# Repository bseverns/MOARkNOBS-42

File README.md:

# MOARkNOBS-42

MOARkNOBS-42 (MN42) is an open, reactive MIDI/OSC performance instrument: a physical control surface, Teensy firmware,
a browser configurator, and a desktop Bridge that are designed and documented as one system.

It gives performers 42 configurable control slots, six envelope-follower inputs, profile recall, MIDI, OSC, and
browser-based editing without hiding the device contract behind proprietary software. It is closer to a small system
with a very visible control surface than “just a controller with a lot of knobs.”

[Try the browser configurator in simulator mode](https://bseverns.github.io/MN42/) without hardware, or read the
[five-minute orientation](docs/getting-started/FirstFiveMinutes.md).

## How the system fits together

```mermaid
flowchart LR
  H[Hardware<br>buttons, pots, LEDs,<br>envelope inputs] --> F[Firmware<br>scanning, MIDI,<br>config, persistence]
  F --> C[Contracts<br>manifest, schema,<br>WebSerial, Bridge RPC]
  C --> U[User tools<br>browser configurator,<br>OSC and host MIDI]
```

Each layer reports what it knows to the next. That is why the project emphasizes schema compatibility, verified
readback, test coverage, and evidence-backed support boundaries.

## Choose your path

| Interest | Start here | You will learn... |
| --- | --- | --- |
| Performer | [Quickstart for Performers](docs/getting-started/QuickstartForPerformers.md) | How to connect, configure, recall profiles, and prepare a rig. |
| Builder | [Quickstart for Builders](docs/getting-started/QuickstartForBuilders.md) | How to inspect, flash, bring up, and validate a board. |
| Contributor | [Contributing](CONTRIBUTING.md) | The build, test, documentation, and review gates. |
| Technical Evaluator | [Hardware-Test Readme](HARDWARE_TEST_README.md) | What the current prototype evidence proves—and does not prove. |

For a conceptual tour, use [Start Here](docs/getting-started/StartHere.md). For a complete source-tree map, use
[Repository Contents](docs/project/RepositoryContents.md).

## What is included

- **Hardware:** a Teensy 4.0 control surface with buttons, pots, LEDs, MIDI I/O, OLED feedback, and six reactive inputs.
- **Firmware:** scheduling, control scanning, MIDI behavior, modulation, configuration, and generation-checked persistence.
- **Browser configurator:** direct WebSerial setup, monitoring, staged edits, verified Apply, profiles, and a hardware-free simulator.
- **Bridge:** local browser console, OSC routing, virtual/host MIDI routing, and an App-over-Bridge transport.
- **Documentation and evidence:** contracts, build guides, validation procedures, and dated bench receipts.

## Quick start without hardware

1. Open the [hosted configurator](https://bseverns.github.io/MN42/).
2. Select **Start Simulator** for the firmware-default reset state, or **Load Demo Rig** for the illustrative example.
3. Check the named simulator fixture in Session, then change a slot, inspect the staged diff, and apply it to the simulated device.

The simulator demonstrates the browser workflow. It does not validate physical controls, timing, MIDI wiring, or
electrical behavior.

## Build and test

The PlatformIO project root is `firmware/`; always pass `-d firmware` from the repository root:

```bash
pio run -d firmware -e teensy40_main
pio test -d firmware -e teensy40_unity -vvv
```

Run the grouped repository checks before proposing a change:

```bash
./tools/doctor --full
```

See [Contributing](CONTRIBUTING.md) for the scoped test matrix and the custom Unity transport rules.

## Current project boundary

MN42 is at the hardware-test stage. The prototype boards and software paths are useful for bring-up and evaluation,
but the repository does not claim a public v1.0 release, an orderable fabrication package, universal host/browser
support, or a signed desktop installer.

Current hardware observations, board photos, test status, and the exact evidence still needed are kept in the
[Hardware-Test Readme](HARDWARE_TEST_README.md) and [Current Build](hardware/CurrentBuild.md)—not on this landing page.

## Documentation

- [Documentation site](https://bseverns.github.io/MOARkNOBS-42/)
- [System Map](docs/getting-started/SystemMap.md)
- [Connectivity Guide](docs/getting-started/ConnectivityGuide.md)
- [Documentation Truth Map](docs/reference/DocumentationTruthMap.md)
- [Testing](docs/validation/TESTING.md)
- [Release and reproducibility](REPRODUCIBILITY.md)

If two documents disagree, the [Documentation Truth Map](docs/reference/DocumentationTruthMap.md) defines the tie-break
rules. Historical wiki pages are frozen; canonical maintained documentation lives in this repository and the generated
documentation site.

## Contact and feedback

- Reproducible bugs and public questions: [GitHub Issues](https://github.com/bseverns/MOARkNOBS-42/issues)
- Security-sensitive reports: [Security policy](SECURITY.md)
- Pilot-run inquiries: [severns3@gmail.com](mailto:severns3@gmail.com)

Never put credentials, private device data, or other secrets in a public issue.

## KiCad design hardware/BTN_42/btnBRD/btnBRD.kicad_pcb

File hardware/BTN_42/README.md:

# BTN_42 Hardware

> The button board that turns the firmware's dreams into something you can actually solder. Pure DIY attitude.

## MN42-1

The `MN42-1` folder holds the first PCB revision:

- [BOM_btnBRD_btnBRD_2025-04-17.xlsx](MN42-1/BOM_btnBRD_btnBRD_2025-04-17.xlsx) – complete bill of materials.
- [PickAndPlace_btnBRD_2025-04-17.xlsx](MN42-1/PickAndPlace_btnBRD_2025-04-17.xlsx) – reference positions for automated assembly.
- [Gerber_btnBRD_2025-04-17.zip](MN42-1/Gerber_btnBRD_2025-04-17.zip) – ready-to-send fabrication package.
- `shell/` – STEP and STL models of the enclosure. `3DShell_btnBRD/` holds the STEP files, while `stl/` contains printable STL meshes.

Sketch diagrams live in [`sketch/`](sketch/). The `PNG_btnBRD_2025-07-22` folder contains exported PNG screenshots of the full EasyEDA schematic.

### Sketch Documents

* [buttonMatrix.md](sketch/buttonMatrix.md)
* [power&protection.md](sketch/power&protection.md)
* [teensy&headers.md](sketch/teensy&headers.md)
* [led&midiOut.md](sketch/led&midiOut.md)
* [midiOpto.md](sketch/midiOpto.md)
* [envelopeFE.md](sketch/envelopeFE.md)
* [display.md](sketch/display.md)

Below is a summary of the schematic sheets:

| Sheet # | Title                                  | Contents                                                                                       |
| ------- | -------------------------------------- | ---------------------------------------------------------------------------------------------- |
| 1       | Title / Block Diagram                  | Topology overview; signal & power flow.                                                        |
| 2       | **Power & Protection**                 | DC jack, F1 logic PTC, TVS, bulk caps, F2 LED PTC, VLED cap, regulators note (Teensy onboard). |
| 3       | **Teensy Core & Headers**              | Teensy 4.0 pinout subset used; I2C to OLED; SPI/unused pads; boot/reset.                       |
| 4       | **Key Matrix & MUX**                   | 42 switches + diodes; 2×CD74HC4067 (or # actually used); row/col nets labelled; OE pull-ups.   |
| 5       | **Level-Shifter & LED / MIDI OUT**     | SN74HCT245, RLED 33 Ω, MIDI OUT loop resistors, DIN connector.                                 |
| 6       | **MIDI IN Opto + ESD**                 | 6N138 (or alt), input resistors, 3V3 pull-up, optional activity LED.                           |
| 7       | **Envelope Follower Analog Front-End** | 6 channels: audio jack (or header), rectifier, RC, clamp to 3V3, into ADC pins.                |
| 8       | **Display, UI, Aux Headers**           | SSD1306 (I²C), spare expansion header (5V, 3V3, SDA, SCL, GND), debug SWD pads.                |
| 9       | Netlist summary / BOM cross-ref.       |                                                                                                |

## License

All hardware files are released under the MIT License, matching the rest of this repository. See the [LICENSE](../../LICENSE) file for details.

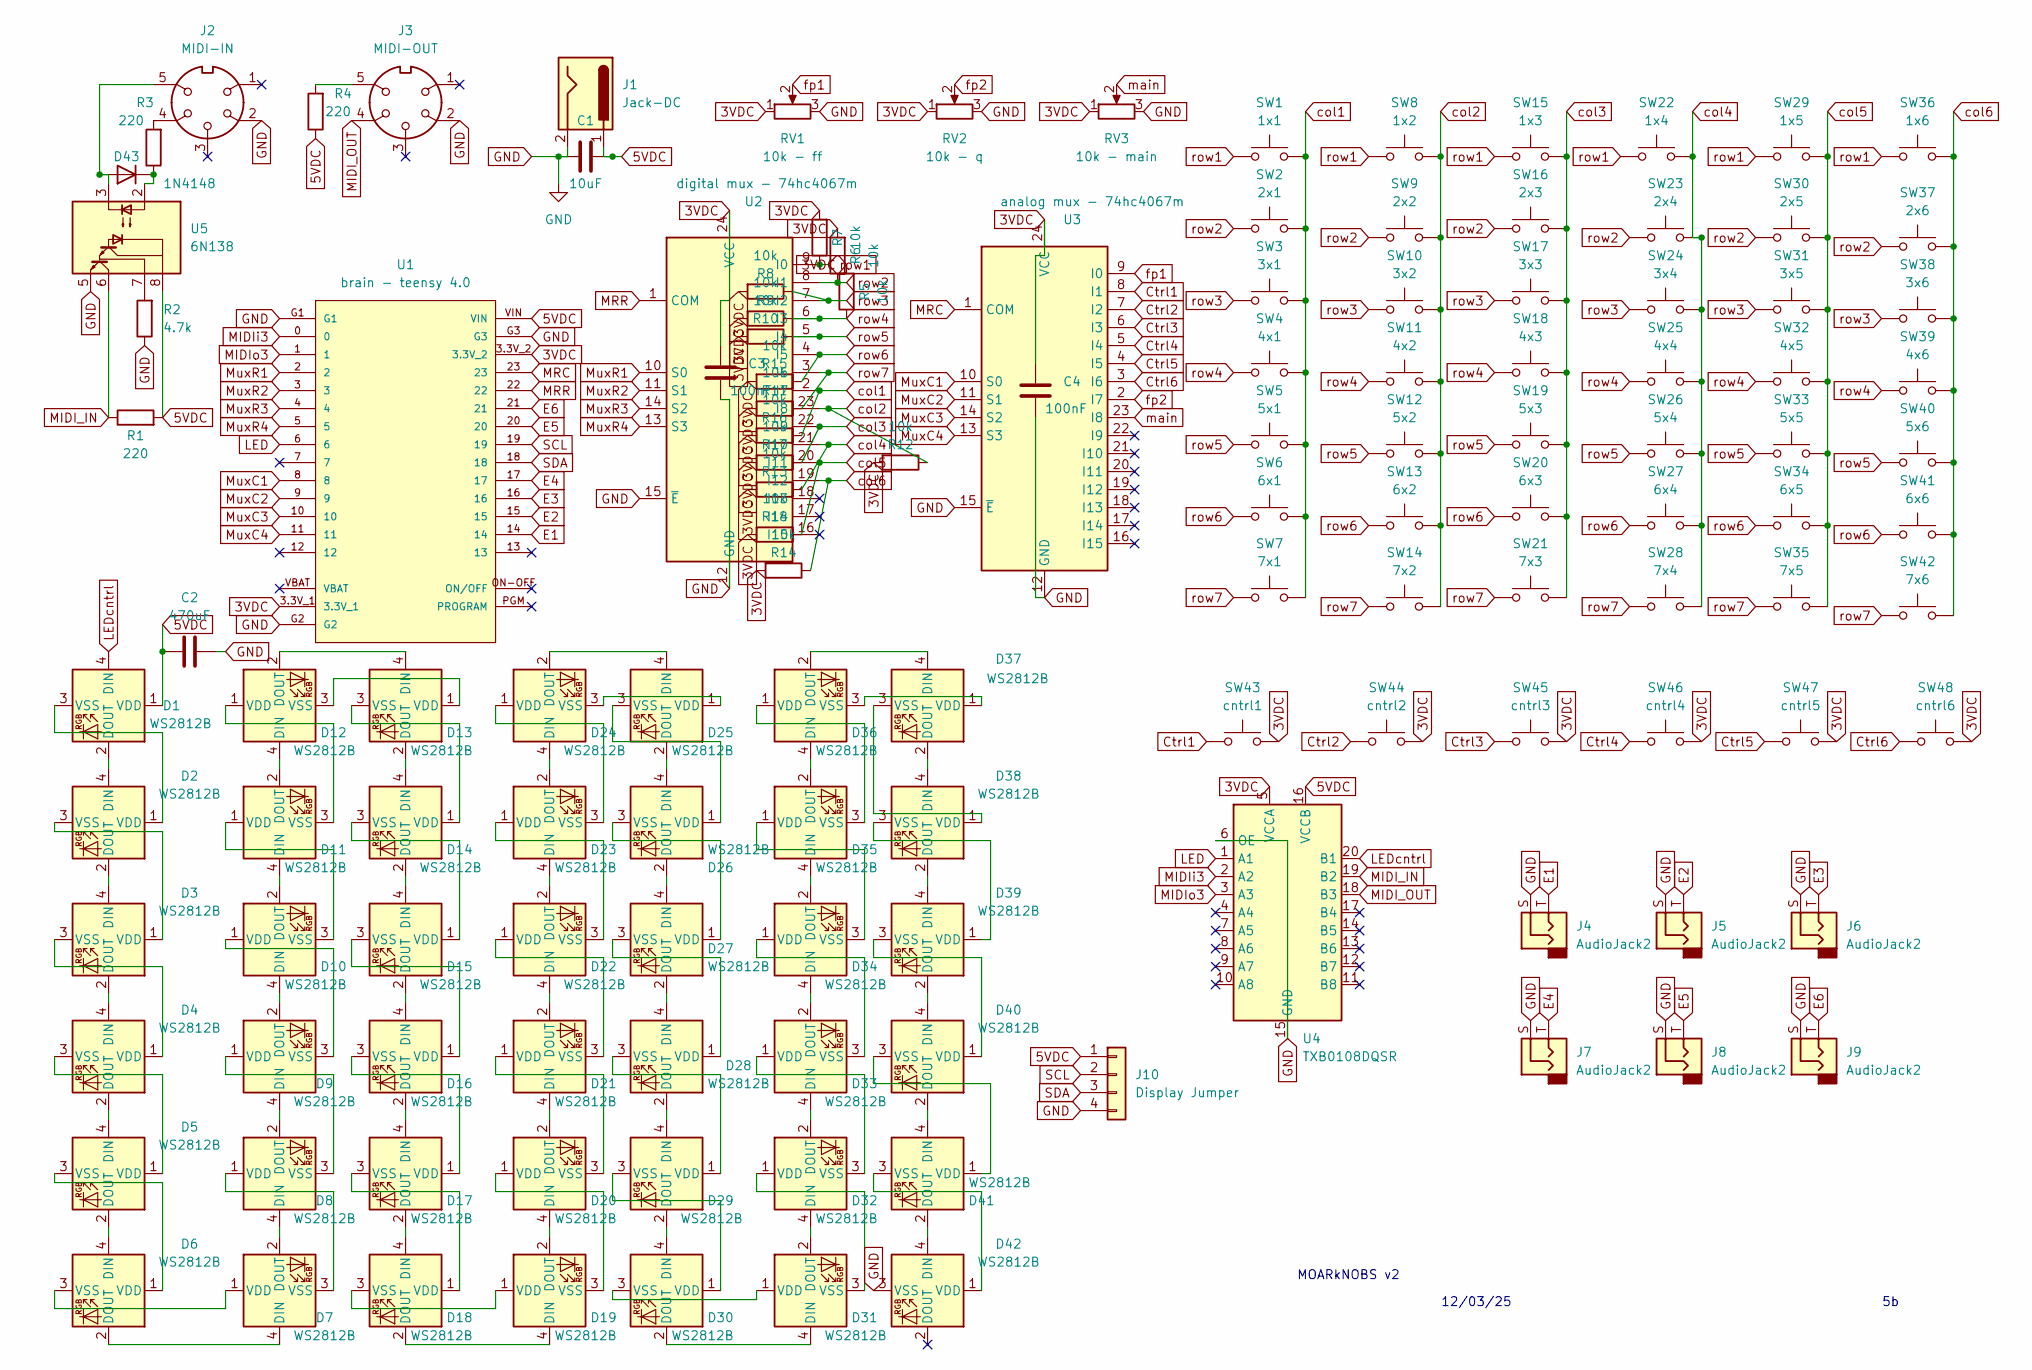
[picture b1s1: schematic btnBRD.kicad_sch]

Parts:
C1: 10uF; C_Disc_D3.4mm_W2.1mm_P2.50mm
C2: 470uF; C_Disc_D3.4mm_W2.1mm_P2.50mm
C3, C4: 100nF; C_Disc_D3.4mm_W2.1mm_P2.50mm
D1, D2, D3, D4, D5, D6, D7, D8, D9, D10, D11, D12, D13, D14, D15, D16, D17, D18, D19, D20, D21, D22, D23, D24, D25, D26, D27, D28, D29, D30, D31, D32, D33, D34, D35, D36, D37, D38, D39, D40, D41, D42: WS2812B; LED_WS2812B_PLCC4_5.0x5.0mm_P3.2mm
D43: 1N4148; D_DO-35_SOD27_P7.62mm_Horizontal
J1: Jack-DC; BarrelJack_GCT_DCJ200-10-A_Horizontal
J2: MIDI-IN; KYCON_KCDX-5S-N
J3: MIDI-OUT; KYCON_KCDX-5S-N
J4, J5, J6, J7, J8, J9: AudioJack2; Jack_3.5mm_CUI_SJ1-3533NG_Horizontal
J10: Display Jumper; JST_EH_S4B-EH_1x04_P2.50mm_Horizontal
R1, R3, R4: 220; R_Axial_DIN0204_L3.6mm_D1.6mm_P2.54mm_Vertical
R2: 4.7k; R_Axial_DIN0204_L3.6mm_D1.6mm_P2.54mm_Vertical
R5, R6, R7, R8, R9, R10, R11, R12, R13, R14, R15, R16, R17, R18: 10k; R_Axial_DIN0204_L3.6mm_D1.6mm_P2.54mm_Vertical
RV1: 10k - ff; Potentiometer_Alps_RK09L_Single_Vertical
RV2: 10k - q; Potentiometer_Alps_RK09L_Single_Vertical
RV3: 10k - main; Potentiometer_Alps_RK09L_Single_Vertical
SW1: 1x1; SW_SPST_PTS645
SW2: 2x1; SW_SPST_PTS645
SW3: 3x1; SW_SPST_PTS645
SW4: 4x1; SW_SPST_PTS645
SW5: 5x1; SW_SPST_PTS645
SW6: 6x1; SW_SPST_PTS645
SW7: 7x1; SW_SPST_PTS645
SW8: 1x2; SW_SPST_PTS645
SW9: 2x2; SW_SPST_PTS645
SW10: 3x2; SW_SPST_PTS645
SW11: 4x2; SW_SPST_PTS645
SW12: 5x2; SW_SPST_PTS645
SW13: 6x2; SW_SPST_PTS645
SW14: 7x2; SW_SPST_PTS645
SW15: 1x3; SW_SPST_PTS645
SW16: 2x3; SW_SPST_PTS645
SW17: 3x3; SW_SPST_PTS645
SW18: 4x3; SW_SPST_PTS645
SW19: 5x3; SW_SPST_PTS645
SW20: 6x3; SW_SPST_PTS645
SW21: 7x3; SW_SPST_PTS645
SW22: 1x4; SW_SPST_PTS645
SW23: 2x4; SW_SPST_PTS645
SW24: 3x4; SW_SPST_PTS645
SW25: 4x4; SW_SPST_PTS645
SW26: 5x4; SW_SPST_PTS645
SW27: 6x4; SW_SPST_PTS645
SW28: 7x4; SW_SPST_PTS645
SW29: 1x5; SW_SPST_PTS645
SW30: 2x5; SW_SPST_PTS645
SW31: 3x5; SW_SPST_PTS645
SW32: 4x5; SW_SPST_PTS645
SW33: 5x5; SW_SPST_PTS645
SW34: 6x5; SW_SPST_PTS645
SW35: 7x5; SW_SPST_PTS645
SW36: 1x6; SW_SPST_PTS645
SW37: 2x6; SW_SPST_PTS645
SW38: 3x6; SW_SPST_PTS645
SW39: 4x6; SW_SPST_PTS645
SW40: 5x6; SW_SPST_PTS645
SW41: 6x6; SW_SPST_PTS645
SW42: 7x6; SW_SPST_PTS645
SW43: cntrl1; SW_SPST_PTS645
SW44: cntrl2; SW_SPST_PTS645
SW45: cntrl3; SW_SPST_PTS645
SW46: cntrl4; SW_SPST_PTS645
SW47: cntrl5; SW_SPST_PTS645
SW48: cntrl6; SW_SPST_PTS645
U1: brain - teensy 4.0; MODULE_DEV-15583
U2: digital mux - 74hc4067m; SOIC-24W_7.5x15.4mm_P1.27mm
U3: analog mux - 74hc4067m; SOIC-24W_7.5x15.4mm_P1.27mm
U4: TXB0108DQSR; USON-20_2x4mm_P0.4mm
U5: 6N138; DIP-8_W7.62mm

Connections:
3VDC: C3.2, C4.2, R5.2, R6.2, R7.2, R8.2, R9.2, R10.2, R11.2, R12.2, R13.2, R14.2, R15.2, R16.2, R17.2, R18.2, RV1.1, RV2.1, RV3.1, SW43.2, SW44.2, SW45.2, SW46.2, SW47.2, SW48.2, U1.3.3V_1, U1.3.3V_2, U2.24 (VCC), U3.24 (VCC), U4.5 (VCCA)
5VDC: C1.2, C2.1, D1.1 (VDD), J1.1, J10.1, R1.2, R4.1, U1.VIN, U4.16 (VCCB), U5.8 (VCC)
Ctrl1: SW43.1, U3.8 (I1)
Ctrl2: SW44.1, U3.7 (I2)
Ctrl3: SW45.1, U3.6 (I3)
Ctrl4: SW46.1, U3.5 (I4)
Ctrl5: SW47.1, U3.4 (I5)
Ctrl6: SW48.1, U3.3 (I6)
E1: J4.T, U1.14
E2: J5.T, U1.15
E3: J6.T, U1.16
E4: J7.T, U1.17
E5: J8.T, U1.20
E6: J9.T, U1.21
GND: C1.1, C2.2, C3.1, C4.1, D42.3 (VSS), J1.2, J2.2, J3.2, J4.S, J5.S, J6.S, J7.S, J8.S, J9.S, J10.4, R2.1, RV1.3, RV2.3, RV3.3, U1.G1, U1.G2, U1.G3, U2.12 (GND), U2.15 (~E), U3.12 (GND), U3.15 (~E), U4.6 (OE), U4.15 (GND), U5.5 (GND)
LED: U1.6, U4.1 (A1)
LEDcntrl: D1.4 (DIN), U4.20 (B1)
MIDI_IN: R1.1, U4.19 (B2), U5.6 (VO2)
MIDI_OUT: J3.4, U4.18 (B3)
MIDIi3: U1.0, U4.2 (A2)
MIDIo3: U1.1, U4.3 (A3)
MRC: U1.23, U3.1 (COM)
MRR: U1.22, U2.1 (COM)
MuxC1: U1.8, U3.10 (S0)
MuxC2: U1.9, U3.11 (S1)
MuxC3: U1.10, U3.14 (S2)
MuxC4: U1.11, U3.13 (S3)
MuxR1: U1.2, U2.10 (S0)
MuxR2: U1.3, U2.11 (S1)
MuxR3: U1.4, U2.14 (S2)
MuxR4: U1.5, U2.13 (S3)
unnamed: D1.2 (DOUT), D2.4 (DIN)
unnamed: D1.3 (VSS), D2.1 (VDD)
unnamed: D2.2 (DOUT), D3.4 (DIN)
unnamed: D2.3 (VSS), D3.1 (VDD)
unnamed: D3.2 (DOUT), D4.4 (DIN)
unnamed: D3.3 (VSS), D4.1 (VDD)
unnamed: D4.2 (DOUT), D5.4 (DIN)
unnamed: D4.3 (VSS), D5.1 (VDD)
unnamed: D5.2 (DOUT), D6.4 (DIN)
unnamed: D5.3 (VSS), D6.1 (VDD)
unnamed: D6.2 (DOUT), D7.4 (DIN)
unnamed: D6.3 (VSS), D7.1 (VDD)
unnamed: D7.2 (DOUT), D8.4 (DIN)
unnamed: D7.3 (VSS), D8.1 (VDD)
unnamed: D8.2 (DOUT), D9.4 (DIN)
unnamed: D8.3 (VSS), D9.1 (VDD)
unnamed: D9.3 (VSS), D10.1 (VDD)
unnamed: D10.2 (DOUT), D11.4 (DIN)
unnamed: D10.3 (VSS), D11.1 (VDD)
unnamed: D9.2 (DOUT), D10.4 (DIN)
unnamed: D11.2 (DOUT), D12.4 (DIN)
unnamed: D11.3 (VSS), D12.1 (VDD)
unnamed: D12.2 (DOUT), D13.4 (DIN)
unnamed: D12.3 (VSS), D13.1 (VDD)
unnamed: D13.2 (DOUT), D14.4 (DIN)
unnamed: D13.3 (VSS), D14.1 (VDD)
unnamed: D14.2 (DOUT), D15.4 (DIN)
unnamed: D14.3 (VSS), D15.1 (VDD)
unnamed: D15.2 (DOUT), D16.4 (DIN)
unnamed: D15.3 (VSS), D16.1 (VDD)
unnamed: D16.2 (DOUT), D17.4 (DIN)
unnamed: D16.3 (VSS), D17.1 (VDD)
unnamed: D17.2 (DOUT), D18.4 (DIN)
unnamed: D17.3 (VSS), D18.1 (VDD)
unnamed: D18.2 (DOUT), D19.4 (DIN)
unnamed: D18.3 (VSS), D19.1 (VDD)
unnamed: D19.2 (DOUT), D20.4 (DIN)
unnamed: D19.3 (VSS), D20.1 (VDD)
unnamed: D20.2 (DOUT), D21.4 (DIN)
unnamed: D20.3 (VSS), D21.1 (VDD)
unnamed: D21.2 (DOUT), D22.4 (DIN)
unnamed: D21.3 (VSS), D22.1 (VDD)
unnamed: D22.2 (DOUT), D23.4 (DIN)
unnamed: D22.3 (VSS), D23.1 (VDD)
unnamed: D23.2 (DOUT), D24.4 (DIN)
unnamed: D23.3 (VSS), D24.1 (VDD)
unnamed: D24.2 (DOUT), D25.4 (DIN)
unnamed: D24.3 (VSS), D25.1 (VDD)
unnamed: D25.2 (DOUT), D26.4 (DIN)
unnamed: D25.3 (VSS), D26.1 (VDD)
unnamed: D26.2 (DOUT), D27.4 (DIN)
unnamed: D26.3 (VSS), D27.1 (VDD)
unnamed: D27.2 (DOUT), D28.4 (DIN)
unnamed: D27.3 (VSS), D28.1 (VDD)
unnamed: D28.2 (DOUT), D29.4 (DIN)
unnamed: D28.3 (VSS), D29.1 (VDD)
unnamed: D29.2 (DOUT), D30.4 (DIN)
unnamed: D29.3 (VSS), D30.1 (VDD)
unnamed: D30.2 (DOUT), D31.4 (DIN)
unnamed: D30.3 (VSS), D31.1 (VDD)
unnamed: D31.2 (DOUT), D32.4 (DIN)
unnamed: D31.3 (VSS), D32.1 (VDD)
unnamed: D32.2 (DOUT), D33.4 (DIN)
unnamed: D32.3 (VSS), D33.1 (VDD)
unnamed: D33.2 (DOUT), D34.4 (DIN)
unnamed: D33.3 (VSS), D34.1 (VDD)
unnamed: D34.2 (DOUT), D35.4 (DIN)
unnamed: D34.3 (VSS), D35.1 (VDD)
unnamed: D35.2 (DOUT), D36.4 (DIN)
unnamed: D35.3 (VSS), D36.1 (VDD)
unnamed: D36.2 (DOUT), D37.4 (DIN)
unnamed: D36.3 (VSS), D37.1 (VDD)
unnamed: D37.2 (DOUT), D38.4 (DIN)
unnamed: D37.3 (VSS), D38.1 (VDD)
unnamed: D38.2 (DOUT), D39.4 (DIN)
unnamed: D38.3 (VSS), D39.1 (VDD)
unnamed: D39.2 (DOUT), D40.4 (DIN)
unnamed: D39.3 (VSS), D40.1 (VDD)
unnamed: D40.2 (DOUT), D41.4 (DIN)
unnamed: D40.3 (VSS), D41.1 (VDD)
unnamed: D41.2 (DOUT), D42.4 (DIN)
unnamed: D41.3 (VSS), D42.1 (VDD)
unnamed: D43.1 (K), R3.1, U5.2 (C1)
unnamed: D43.2 (A), J2.5, U5.3 (C2)
unnamed: J2.4, R3.2
unnamed: J3.5, R4.2
unnamed: R2.2, U5.7 (VO1)
SCL: J10.2, U1.19
SDA: J10.3, U1.18
col1: R16.1, SW1.2, SW2.2, SW3.2, SW4.2, SW5.2, SW6.2, SW7.2, U2.2 (I7)
col2: R12.1, SW8.2, SW9.2, SW10.2, SW11.2, SW12.2, SW13.2, SW14.2, U2.23 (I8)
col3: R17.1, SW15.2, SW16.2, SW17.2, SW18.2, SW19.2, SW20.2, SW21.2, U2.22 (I9)
col4: R13.1, SW22.2, SW23.2, SW24.2, SW25.2, SW26.2, SW27.2, SW28.2, U2.21 (I10)
col5: R18.1, SW29.2, SW30.2, SW31.2, SW32.2, SW33.2, SW34.2, SW35.2, U2.20 (I11)
col6: R14.1, SW36.2, SW37.2, SW38.2, SW39.2, SW40.2, SW41.2, SW42.2, U2.19 (I12)
fp1: RV1.2, U3.9 (I0)
fp2: RV2.2, U3.2 (I7)
main: RV3.2, U3.23 (I8)
row1: R7.1, SW1.1, SW8.1, SW15.1, SW22.1, SW29.1, SW36.1, U2.9 (I0)
row2: R6.1, SW2.1, SW9.1, SW16.1, SW23.1, SW30.1, SW37.1, U2.8 (I1)
row3: R8.1, SW3.1, SW10.1, SW17.1, SW24.1, SW31.1, SW38.1, U2.7 (I2)
row4: R5.1, R9.1, SW4.1, SW11.1, SW18.1, SW25.1, SW32.1, SW39.1, U2.6 (I3)
row5: R10.1, SW5.1, SW12.1, SW19.1, SW26.1, SW33.1, SW40.1, U2.5 (I4)
row6: R15.1, SW6.1, SW13.1, SW20.1, SW27.1, SW34.1, SW41.1, U2.4 (I5)
row7: R11.1, SW7.1, SW14.1, SW21.1, SW28.1, SW35.1, SW42.1, U2.3 (I6)

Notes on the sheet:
12/03/25
MOARkNOBS v2

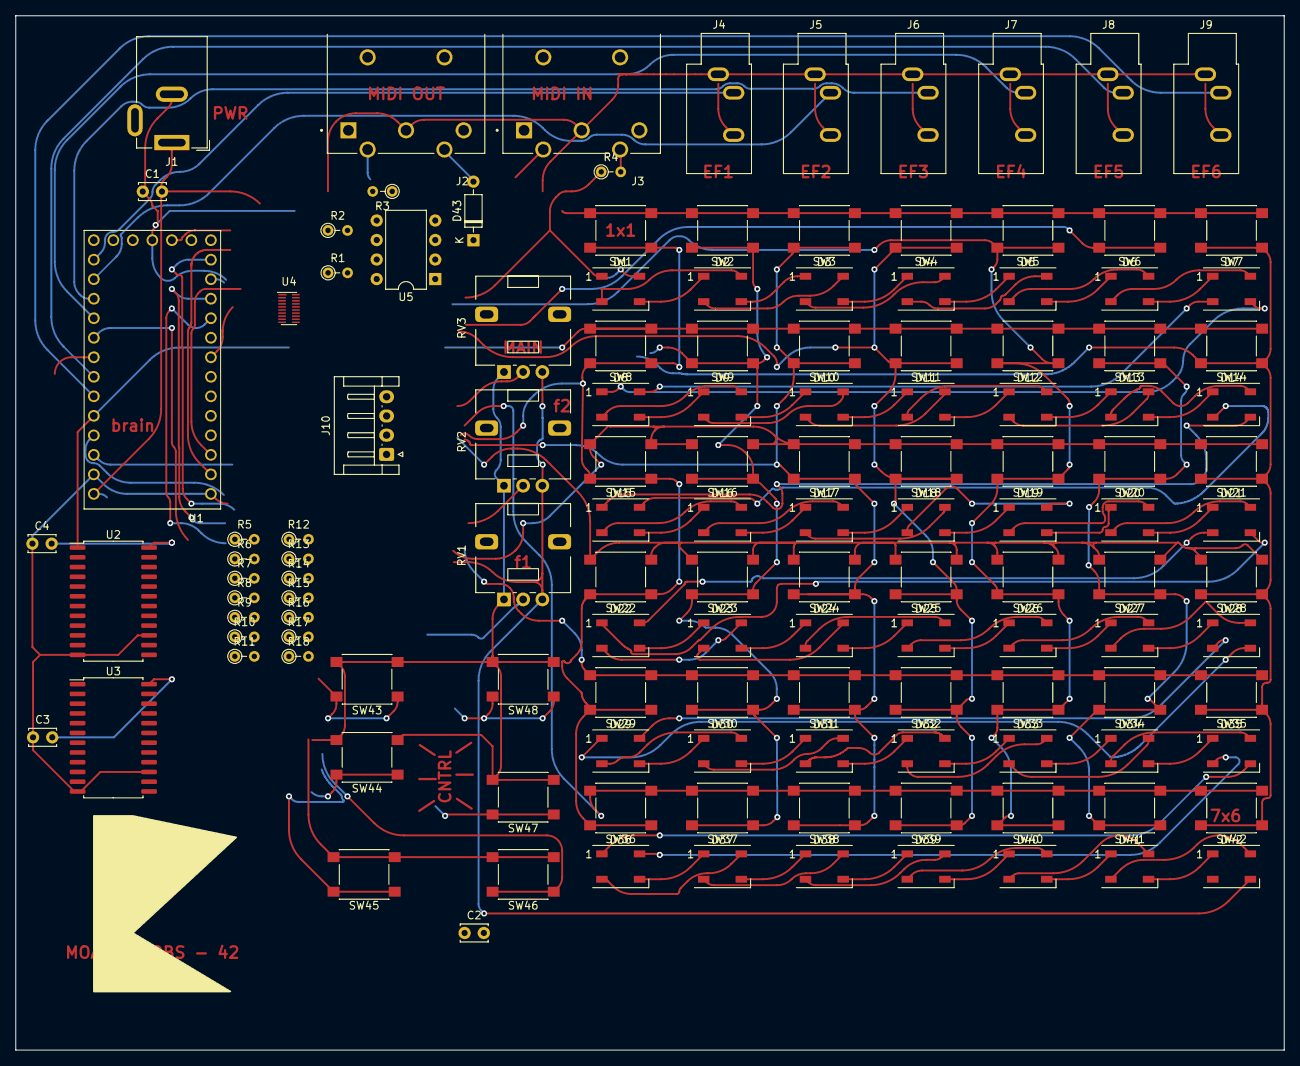
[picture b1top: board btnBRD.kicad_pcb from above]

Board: 2 copper layers, 165.1 x 134.6 mm, 131 parts (0 on the bottom side), 136 nets.

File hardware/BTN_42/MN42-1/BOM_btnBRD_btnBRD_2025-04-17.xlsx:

No. | Quantity | Comment | Designator | Footprint | Value | Manufacturer Part | Manufacturer | Supplier Part | Supplier
1 | 1 | 10uF | C1 | CAP-TH_L5.5-W3.5-P5.00-D0.5 | 10uF | FG26X7R1E106KRT06 | TDK | C531341 | LCSC
2 | 3 | 100nF | C2,C3,C4 | CAP-TH_L5.0-W4.0-P5.00-D1.0 | 100nF | CT4G-0805-2X1-63V-0.1μF-K | TORCH(火炬) | C400087 | LCSC
3 | 42 | XL-5050RGBC-WS2812B | D1,D2,D3,D4,D5,D6,D7,D8,D9,D10,D11,D12,D13,D14,D15,D16,D17,D18,D19,D20,D21,D22,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 | LED-SMD_4P-L5.0-W5.0-BL_XL-5050RGBC |  | XL-5050RGBC-WS2812B | XINGLIGHT(成兴光) | C2843785 | LCSC
4 | 1 | 1N4148PF | D43 | DO-35_BD1.9-L3.9-P7.90-D0.5-FD |  | 1N4148PF | ST(先科) | C2992430 | LCSC
5 | 1 | DC005 | J1 | DC-IN-TH_DC005 |  | DC005 | SHOU HAN(首韩) | C431533 | LCSC
6 | 2 | DIN-504B-M10 | J2,J3 | CONN-TH_DIN-504B-M10 |  | DIN-504B-M10 | HOOYA(皓宇电子) | C2939346 | LCSC
7 | 6 | HC-PJ-320A | J4,J5,J6,J7,J8,J9 | AUDIO-SMD_HC-PJ-320A |  | HC-PJ-320A | HC(虹成电子) | C7501806 | LCSC
8 | 1 | HS96L03W2C03 | J10 | OLED-TH_L27.8-W27.2-P2.54_C9900033791 |  | HS96L03W2C03 | HS(汉昇) | C5248080 | LCSC
9 | 3 | 220Ω | R1,R3,R4 | RES-TH_BD1.7-L3.5-P7.50-D0.5 | 220Ω | RN 1/8W 220R F T/B A1 | Tyohm(幸亚电阻) | C433487 | LCSC
10 | 1 | 4.7kΩ | R2 | RES-TH_BD1.7-L3.5-P7.50-D0.5 | 4.7kΩ | RN 1/8W 4K7 F T/B A1 | Tyohm(幸亚电阻) | C433477 | LCSC
11 | 14 | 10kΩ | R5,R6,R7,R8,R9,R10,R11,R12,R13,R14,R15,R16,R17,R18 | RES-TH_BD1.7-L3.5-P7.50-D0.5 | 10kΩ | RN1/8W10KFT/BA1 | Tyohm(幸亚电阻) | C433502 | LCSC
12 | 3 | 10kΩ | RV1,RV2,RV3 | RES-ADJ-TH_RK09K1130A5R | 10kΩ | RK09K1130A5R | ALPSALPINE(阿尔卑斯阿尔派) | C209779 | LCSC
13 | 48 | HX B3F-4055-Y | SW1,SW2,SW3,SW4,SW5,SW6,SW7,SW8,SW9,SW10,SW11,SW12,SW13,SW14,SW15,SW16,SW17,SW1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 | SW-TH_4P-L12.0-W12.0-P5.00-LS12.5 |  | HX B3F-4055-Y | hanxia(韩下) | C36498965 | LCSC
14 | 1 | pwr switch | SW49 | SW-TH_TK-6580A-1 |  | pwr switch | Yuandi(元迪) | C528770 | LCSC
15 | 1 | teensy40_DEV-15583 | U1 | teensy 4.0:MODULE_DEV-15583 | brain - teensy 4.0
16 | 2 | CD74HC4067M96 | U2,U3 | SOIC-24_L15.4-W7.5-P1.27-LS10.3-BL |  | CD74HC4067M96 | TI(德州仪器) | C496123 | LCSC
17 | 1 | TXB0108DQSR | U4 | SON-20_L4.0-W2.0-P0.40-BL |  | TXB0108DQSR | TI(德州仪器) | C427057 | LCSC
18 | 1 | 6N138 | U5 | DIP-8_L9.8-W6.6-P2.54-LS7.6-BL |  | 6N138 | ISOCOM(英国安数光) | C255743 | LCSC

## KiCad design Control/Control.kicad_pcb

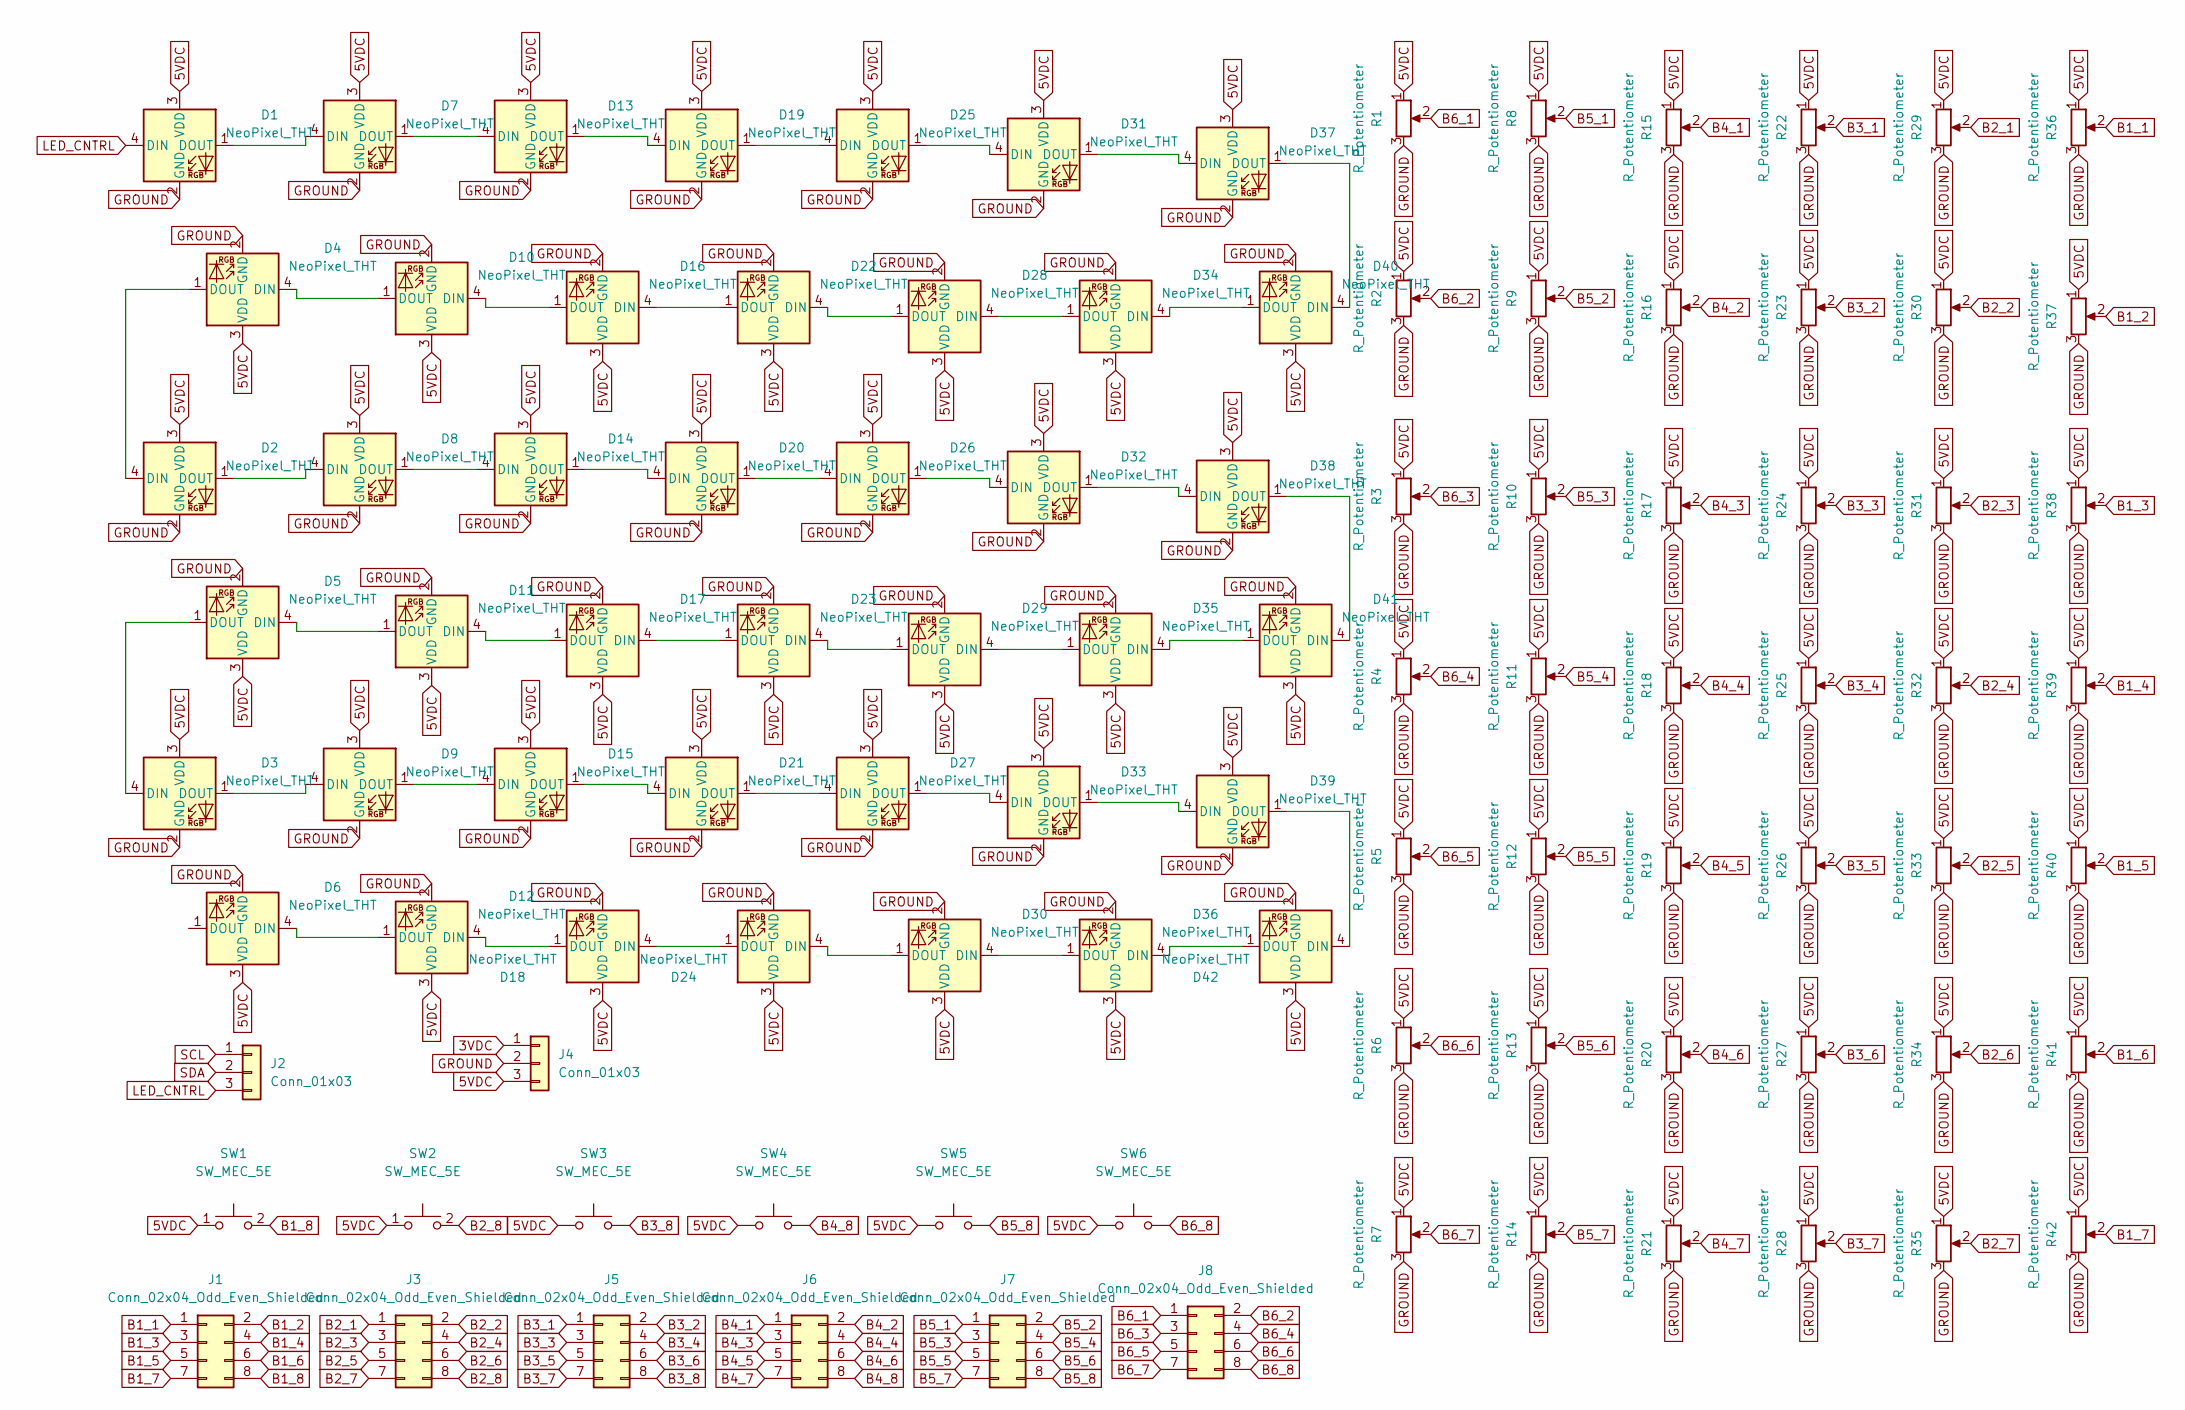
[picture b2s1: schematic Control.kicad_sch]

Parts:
D1, D2, D3, D4, D5, D6, D7, D8, D9, D10, D11, D12, D13, D14, D15, D16, D17, D18, D19, D20, D21, D22, D23, D24, D25, D26, D27, D28, D29, D30, D31, D32, D33, D34, D35, D36, D37, D38, D39, D40, D41, D42: NeoPixel_THT; LED_SK6812MINI_PLCC4_3.5x3.5mm_P1.75mm
J1, J3, J5, J6, J7, J8: Conn_02x04_Odd_Even_Shielded; PinHeader_2x04_P1.00mm_Vertical
J2, J4: Conn_01x03; PinHeader_1x03_P1.00mm_Vertical
R1, R2, R3, R4, R5, R6, R7, R8, R9, R10, R11, R12, R13, R14, R15, R16, R17, R18, R19, R20, R21, R22, R23, R24, R25, R26, R27, R28, R29, R30, R31, R32, R33, R34, R35, R36, R37, R38, R39, R40, R41, R42: R_Potentiometer; Potentiometer_Alps_RK09K_Single_Vertical
SW1, SW2, SW3, SW4, SW5, SW6: SW_MEC_5E; SW_TH_Tactile_Omron_B3F-10xx

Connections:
3VDC: J4.1
5VDC: D1.3 (VDD), D2.3 (VDD), D3.3 (VDD), D4.3 (VDD), D5.3 (VDD), D6.3 (VDD), D7.3 (VDD), D8.3 (VDD), D9.3 (VDD), D10.3 (VDD), D11.3 (VDD), D12.3 (VDD), D13.3 (VDD), D14.3 (VDD), D15.3 (VDD), D16.3 (VDD), D17.3 (VDD), D18.3 (VDD), D19.3 (VDD), D20.3 (VDD), D21.3 (VDD), D22.3 (VDD), D23.3 (VDD), D24.3 (VDD), D25.3 (VDD), D26.3 (VDD), D27.3 (VDD), D28.3 (VDD), D29.3 (VDD), D30.3 (VDD), D31.3 (VDD), D32.3 (VDD), D33.3 (VDD), D34.3 (VDD), D35.3 (VDD), D36.3 (VDD), D37.3 (VDD), D38.3 (VDD), D39.3 (VDD), D40.3 (VDD), D41.3 (VDD), D42.3 (VDD), J4.3, R1.1, R2.1, R3.1, R4.1, R5.1, R6.1, R7.1, R8.1, R9.1, R10.1, R11.1, R12.1, R13.1, R14.1, R15.1, R16.1, R17.1, R18.1, R19.1, R20.1, R21.1, R22.1, R23.1, R24.1, R25.1, R26.1, R27.1, R28.1, R29.1, R30.1, R31.1, R32.1, R33.1, R34.1, R35.1, R36.1, R37.1, R38.1, R39.1, R40.1, R41.1, R42.1, SW1.1, SW2.1, SW3.1, SW4.1, SW5.1, SW6.1
B1_1: J1.1, R36.2
B1_2: J1.2, R37.2
B1_3: J1.3, R38.2
B1_4: J1.4, R39.2
B1_5: J1.5, R40.2
B1_6: J1.6, R41.2
B1_7: J1.7, R42.2
B1_8: J1.8, SW1.2
B2_1: J3.1, R29.2
B2_2: J3.2, R30.2
B2_3: J3.3, R31.2
B2_4: J3.4, R32.2
B2_5: J3.5, R33.2
B2_6: J3.6, R34.2
B2_7: J3.7, R35.2
B2_8: J3.8, SW2.2
B3_1: J5.1, R22.2
B3_2: J5.2, R23.2
B3_3: J5.3, R24.2
B3_4: J5.4, R25.2
B3_5: J5.5, R26.2
B3_6: J5.6, R27.2
B3_7: J5.7, R28.2
B3_8: J5.8, SW3.2
B4_1: J6.1, R15.2
B4_2: J6.2, R16.2
B4_3: J6.3, R17.2
B4_4: J6.4, R18.2
B4_5: J6.5, R19.2
B4_6: J6.6, R20.2
B4_7: J6.7, R21.2
B4_8: J6.8, SW4.2
B5_1: J7.1, R8.2
B5_2: J7.2, R9.2
B5_3: J7.3, R10.2
B5_4: J7.4, R11.2
B5_5: J7.5, R12.2
B5_6: J7.6, R13.2
B5_7: J7.7, R14.2
B5_8: J7.8, SW5.2
B6_1: J8.1, R1.2
B6_2: J8.2, R2.2
B6_3: J8.3, R3.2
B6_4: J8.4, R4.2
B6_5: J8.5, R5.2
B6_6: J8.6, R6.2
B6_7: J8.7, R7.2
B6_8: J8.8, SW6.2
GROUND: D1.2 (GND), D2.2 (GND), D3.2 (GND), D4.2 (GND), D5.2 (GND), D6.2 (GND), D7.2 (GND), D8.2 (GND), D9.2 (GND), D10.2 (GND), D11.2 (GND), D12.2 (GND), D13.2 (GND), D14.2 (GND), D15.2 (GND), D16.2 (GND), D17.2 (GND), D18.2 (GND), D19.2 (GND), D20.2 (GND), D21.2 (GND), D22.2 (GND), D23.2 (GND), D24.2 (GND), D25.2 (GND), D26.2 (GND), D27.2 (GND), D28.2 (GND), D29.2 (GND), D30.2 (GND), D31.2 (GND), D32.2 (GND), D33.2 (GND), D34.2 (GND), D35.2 (GND), D36.2 (GND), D37.2 (GND), D38.2 (GND), D39.2 (GND), D40.2 (GND), D41.2 (GND), D42.2 (GND), J4.2, R1.3, R2.3, R3.3, R4.3, R5.3, R6.3, R7.3, R8.3, R9.3, R10.3, R11.3, R12.3, R13.3, R14.3, R15.3, R16.3, R17.3, R18.3, R19.3, R20.3, R21.3, R22.3, R23.3, R24.3, R25.3, R26.3, R27.3, R28.3, R29.3, R30.3, R31.3, R32.3, R33.3, R34.3, R35.3, R36.3, R37.3, R38.3, R39.3, R40.3, R41.3, R42.3
LED_CNTRL: D1.4 (DIN), J2.3
unnamed: D1.1 (DOUT), D7.4 (DIN)
unnamed: D2.1 (DOUT), D8.4 (DIN)
unnamed: D2.4 (DIN), D4.1 (DOUT)
unnamed: D3.1 (DOUT), D9.4 (DIN)
unnamed: D3.4 (DIN), D5.1 (DOUT)
unnamed: D4.4 (DIN), D10.1 (DOUT)
unnamed: D10.4 (DIN), D16.1 (DOUT)
unnamed: D5.4 (DIN), D11.1 (DOUT)
unnamed: D11.4 (DIN), D17.1 (DOUT)
unnamed: D6.4 (DIN), D12.1 (DOUT)
unnamed: D12.4 (DIN), D18.1 (DOUT)
unnamed: D13.1 (DOUT), D19.4 (DIN)
unnamed: D7.1 (DOUT), D13.4 (DIN)
unnamed: D14.1 (DOUT), D20.4 (DIN)
unnamed: D8.1 (DOUT), D14.4 (DIN)
unnamed: D15.1 (DOUT), D21.4 (DIN)
unnamed: D9.1 (DOUT), D15.4 (DIN)
unnamed: D16.4 (DIN), D22.1 (DOUT)
unnamed: D17.4 (DIN), D23.1 (DOUT)
unnamed: D18.4 (DIN), D24.1 (DOUT)
unnamed: D19.1 (DOUT), D25.4 (DIN)
unnamed: D20.1 (DOUT), D26.4 (DIN)
unnamed: D21.1 (DOUT), D27.4 (DIN)
unnamed: D22.4 (DIN), D28.1 (DOUT)
unnamed: D23.4 (DIN), D29.1 (DOUT)
unnamed: D24.4 (DIN), D30.1 (DOUT)
unnamed: D25.1 (DOUT), D31.4 (DIN)
unnamed: D26.1 (DOUT), D32.4 (DIN)
unnamed: D27.1 (DOUT), D33.4 (DIN)
unnamed: D28.4 (DIN), D34.1 (DOUT)
unnamed: D29.4 (DIN), D35.1 (DOUT)
unnamed: D30.4 (DIN), D36.1 (DOUT)
unnamed: D31.1 (DOUT), D37.4 (DIN)
unnamed: D32.1 (DOUT), D38.4 (DIN)
unnamed: D33.1 (DOUT), D39.4 (DIN)
unnamed: D34.4 (DIN), D40.1 (DOUT)
unnamed: D35.4 (DIN), D41.1 (DOUT)
unnamed: D36.4 (DIN), D42.1 (DOUT)
unnamed: D37.1 (DOUT), D40.4 (DIN)
unnamed: D38.1 (DOUT), D41.4 (DIN)
unnamed: D39.1 (DOUT), D42.4 (DIN)
SCL: J2.1
SDA: J2.2

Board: 2 copper layers, 98 parts (0 on the bottom side), 92 nets, no tracks yet.

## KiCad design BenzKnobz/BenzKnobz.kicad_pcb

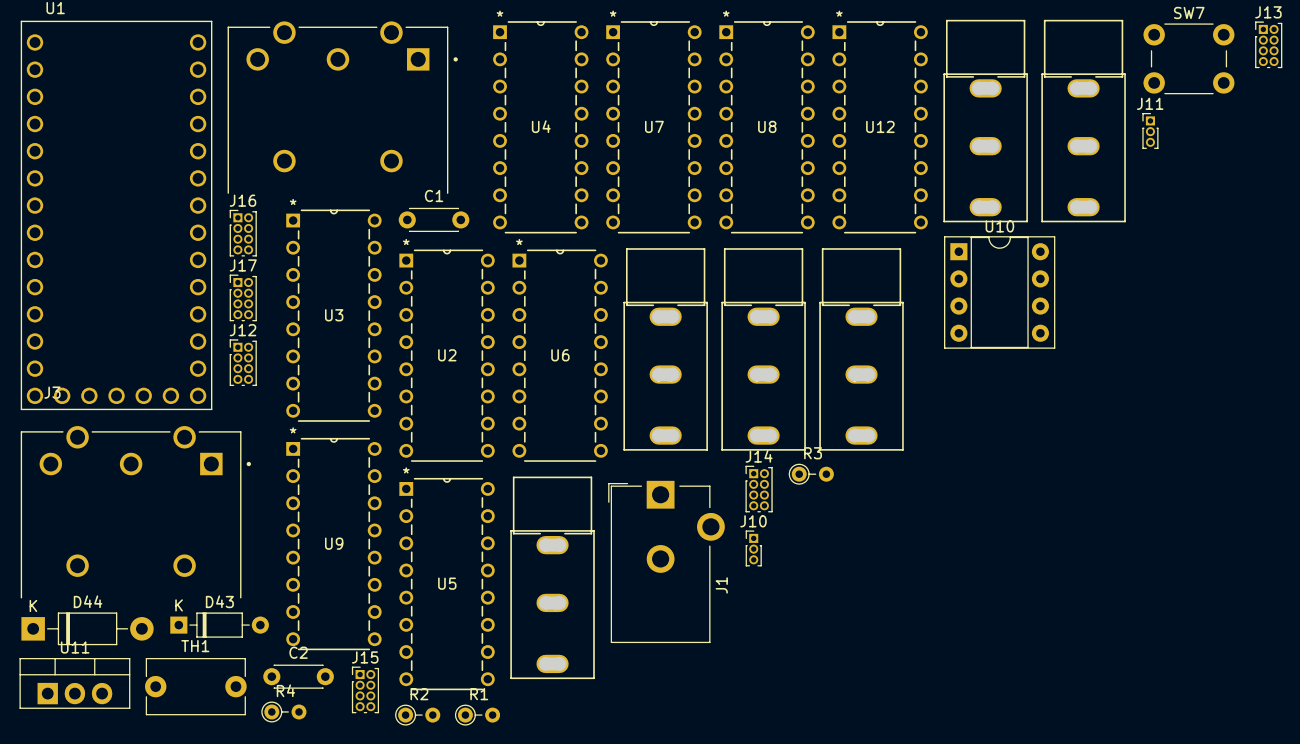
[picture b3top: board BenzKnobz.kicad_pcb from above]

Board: 2 copper layers, 39 parts (0 on the bottom side), 90 nets, no tracks yet.

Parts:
C1, C2: CAP_CERAMIC0402; C_Disc_D4.3mm_W1.9mm_P5.00mm
D43: 1N4148; D_DO-35_SOD27_P7.62mm_Horizontal
D44: 1N4007; D_DO-41_SOD81_P10.16mm_Horizontal
J1: Barrel_Jack; BarrelJack_CUI_PJ-102AH_Horizontal
J2: MIDI OUT; KYCON_KCDX-5S-N
J3: MIDI IN; KYCON_KCDX-5S-N
J4, J5, J6, J7, J8, J9: MJ-3502; CONN_MJ-3502
J10, J11: Conn_01x03; PinHeader_1x03_P1.00mm_Vertical
J12, J13, J14, J15, J16, J17: Conn_02x04_Odd_Even_Shielded; PinHeader_2x04_P1.00mm_Vertical
R1, R2, R3, R4: 220R; R_Axial_DIN0204_L3.6mm_D1.6mm_P2.54mm_Vertical
SW7: SW_Push_SPDT; SW_PUSH_6mm
TH1: Thermistor; C_Disc_D9.0mm_W5.0mm_P7.50mm
U1: teensy 4.0; MODULE_DEV-15583
U2, U12: CD74HC4050E; N16
U3, U4, U5, U6, U7, U8, U9: 74HC4051; N16
U10: 6N138; DIP-8_W7.62mm_Socket
U11: LM317_TO-220; TO-220-3_Vertical

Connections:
3VDC: J11.1, U1.3.3V_2, U12.1 (VCC)
5VDC: J11.3, R2.1, R4.1, TH1.1, U2.1 (VCC), U3.16 (VCC), U4.16 (VCC), U5.16 (VCC), U6.16 (VCC), U7.16 (VCC), U8.16 (VCC), U9.16 (VCC), U10.8 (VCC)
A0: J7.3, U1.14
A1: J6.3, U1.15
A2: J5.3, U1.16
A3: J4.3, U1.17
A4: J8.3, U1.20
A5: J9.3, U1.21
B1_1: J12.1, U4.13 (A0)
B1_2: J12.2, U4.14 (A1)
B1_3: J12.3, U4.15 (A2)
B1_4: J12.4, U4.12 (A3)
B1_5: J12.5, U4.1 (A4)
B1_6: J12.6, U4.5 (A5)
B1_7: J12.7, U4.2 (A6)
B1_8: J12.8, U4.4 (A7)
B2_1: J13.1, U5.13 (A0)
B2_2: J13.2, U5.14 (A1)
B2_3: J13.3, U5.15 (A2)
B2_4: J13.4, U5.12 (A3)
B2_5: J13.5, U5.1 (A4)
B2_6: J13.6, U5.5 (A5)
B2_7: J13.7, U5.2 (A6)
B2_8: J13.8, U5.4 (A7)
B3_1: J14.1, U6.13 (A0)
B3_2: J14.2, U6.14 (A1)
B3_3: J14.3, U6.15 (A2)
B3_4: J14.4, U6.12 (A3)
B3_5: J14.5, U6.1 (A4)
B3_6: J14.6, U6.5 (A5)
B3_7: J14.7, U6.2 (A6)
B3_8: J14.8, U6.4 (A7)
B4_1: J15.1, U7.13 (A0)
B4_2: J15.2, U7.14 (A1)
B4_3: J15.3, U7.15 (A2)
B4_4: J15.4, U7.12 (A3)
B4_5: J15.5, U7.1 (A4)
B4_6: J15.6, U7.5 (A5)
B4_7: J15.7, U7.2 (A6)
B4_8: J15.8, U7.4 (A7)
B5_1: J16.1, U8.13 (A0)
B5_2: J16.2, U8.14 (A1)
B5_3: J16.3, U8.15 (A2)
B5_4: J16.4, U8.12 (A3)
B5_5: J16.5, U8.1 (A4)
B5_6: J16.6, U8.5 (A5)
B5_7: J16.7, U8.2 (A6)
B5_8: J16.8, U8.4 (A7)
B6_1: J17.1, U9.13 (A0)
B6_2: J17.2, U9.14 (A1)
B6_3: J17.3, U9.15 (A2)
B6_4: J17.4, U9.12 (A3)
B6_5: J17.5, U9.1 (A4)
B6_6: J17.6, U9.5 (A5)
B6_7: J17.7, U9.2 (A6)
B6_8: J17.8, U9.4 (A7)
GROUND: C1.2, C2.2, J1.2, J2.2, J4.1, J4.2, J5.1, J5.2, J6.1, J6.2, J7.1, J7.2, J8.1, J8.2, J9.1, J9.2, J11.2, U1.G1, U1.G2, U1.G3, U2.8 (GND), U3.6 (~E), U3.8 (GND), U4.6 (~E), U4.8 (GND), U5.6 (~E), U5.8 (GND), U6.6 (~E), U6.8 (GND), U7.6 (~E), U7.8 (GND), U8.6 (~E), U8.8 (GND), U9.6 (~E), U9.8 (GND), U10.5 (GND), U12.8 (GND)
LED: J10.3, U1.6
M1: U1.7, U2.3 (1A)
M2: U1.8, U2.5 (2A)
M3: U1.9, U2.7 (3A)
M4: U1.10, U2.9 (4A)
M5: U1.11, U2.11 (5A)
M6: U1.12, U2.14 (6A)
MIDI IN: R2.2, U1.0, U10.6 (VO2)
MIDI OUT: R3.2, U1.1
MUX_READ: U1.22, U12.2 (1Y), U12.4 (2Y), U12.6 (3Y), U12.10 (4Y), U12.12 (5Y), U12.15 (6Y)
MuxA1: U2.2 (1Y), U3.11 (S0)
MuxA2: U2.4 (2Y), U3.10 (S1)
MuxA3: U2.6 (3Y), U3.9 (S2)
MuxB1: U2.10 (4Y), U4.11 (S0), U5.11 (S0), U6.11 (S0), U7.11 (S0), U8.11 (S0), U9.11 (S0)
MuxB2: U2.12 (5Y), U4.10 (S1), U5.10 (S1), U6.10 (S1), U7.10 (S1), U8.10 (S1), U9.10 (S1)
MuxB3: U2.15 (6Y), U4.9 (S2), U5.9 (S2), U6.9 (S2), U7.9 (S2), U8.9 (S2), U9.9 (S2)
MuxBD1: U3.13 (A0), U4.3 (A), U12.3 (1A)
MuxBD2: U3.14 (A1), U5.3 (A), U12.5 (2A)
MuxBD3: U3.15 (A2), U6.3 (A), U12.7 (3A)
MuxBD4: U3.12 (A3), U7.3 (A), U12.9 (4A)
MuxBD5: U3.1 (A4), U8.3 (A), U12.11 (5A)
MuxBD6: U3.5 (A5), U9.3 (A), U12.14 (6A)
unnamed: C1.1, C2.1, D44.1 (K), U11.3 (VI)
unnamed: D43.1 (K), R1.2, U10.2 (C1)
unnamed: D43.2 (A), J3.5, U10.3 (C2)
unnamed: D44.2 (A), SW7.1 (A)
unnamed: J2.4, R3.1
unnamed: J2.5, R4.2
unnamed: J3.4, R1.1
unnamed: SW7.2 (B), TH1.2
unnamed: U1.VIN, U11.2 (VO)
SCL: J10.1, U1.19
SDA: J10.2, U1.18
